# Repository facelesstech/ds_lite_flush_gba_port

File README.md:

# ds_lite_flush_gba_port
ds_lite_flush_gba_port

Blog post - https://facelesstech.wordpress.com/2022/10/15/gameboy-macro-with-a-flush-gba-port/

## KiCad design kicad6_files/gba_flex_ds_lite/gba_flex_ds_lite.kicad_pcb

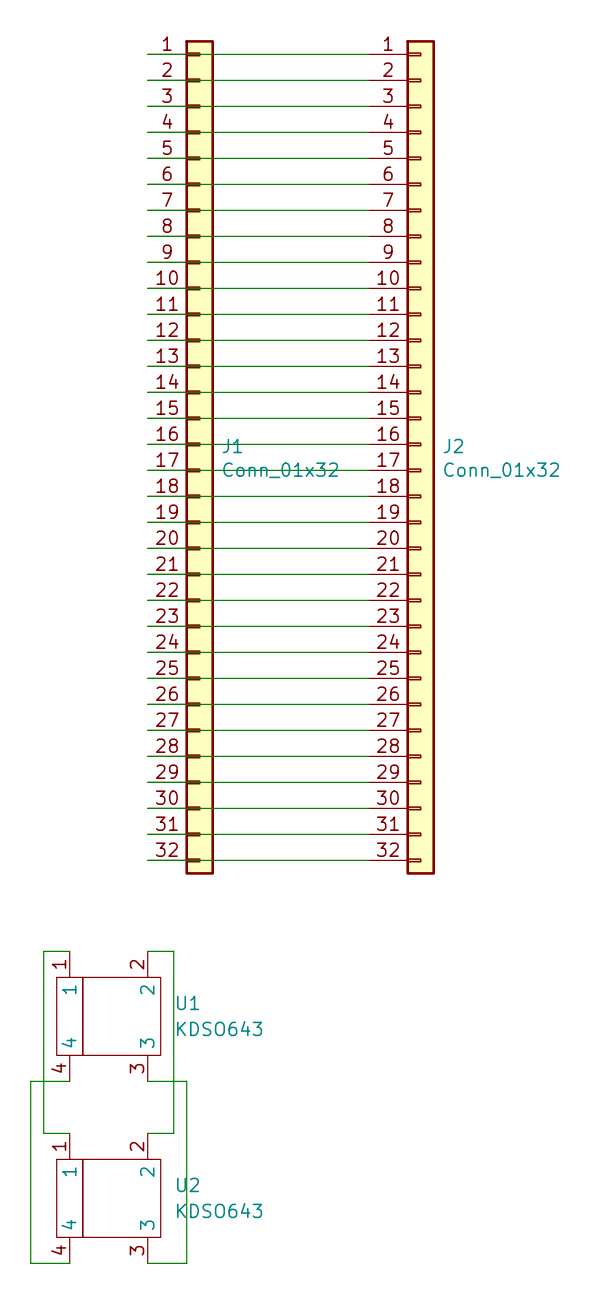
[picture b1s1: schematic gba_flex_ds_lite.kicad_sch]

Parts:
J1: Conn_01x32; GBBus_small
J2: Conn_01x32; GBBus_small_through_hole
U1: KDSO643; ds_lite_crystal_KDSO643_TH
U2: KDSO643; ds_lite_crystal_KDSO643_SMD

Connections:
unnamed: J1.1, J2.1
unnamed: J1.2, J2.2
unnamed: J1.3, J2.3
unnamed: J1.4, J2.4
unnamed: J1.5, J2.5
unnamed: J1.6, J2.6
unnamed: J1.7, J2.7
unnamed: J1.8, J2.8
unnamed: J1.9, J2.9
unnamed: J1.10, J2.10
unnamed: J1.11, J2.11
unnamed: J1.12, J2.12
unnamed: J1.13, J2.13
unnamed: J1.14, J2.14
unnamed: J1.15, J2.15
unnamed: J1.16, J2.16
unnamed: J1.17, J2.17
unnamed: J1.18, J2.18
unnamed: J1.19, J2.19
unnamed: J1.20, J2.20
unnamed: J1.21, J2.21
unnamed: J1.22, J2.22
unnamed: J1.23, J2.23
unnamed: J1.24, J2.24
unnamed: J1.25, J2.25
unnamed: J1.26, J2.26
unnamed: J1.27, J2.27
unnamed: J1.28, J2.28
unnamed: J1.29, J2.29
unnamed: J1.30, J2.30
unnamed: J1.31, J2.31
unnamed: J1.32, J2.32
unnamed: U1.1, U2.1
unnamed: U1.2, U2.2
unnamed: U1.3, U2.3
unnamed: U1.4, U2.4

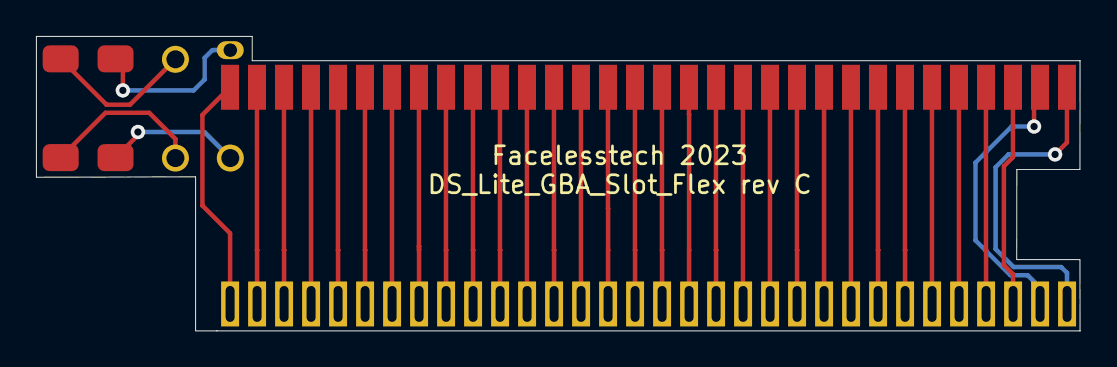
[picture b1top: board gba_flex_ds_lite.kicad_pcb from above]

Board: 2 copper layers, 58.0 x 16.4 mm, 4 parts (0 on the bottom side), 36 nets.

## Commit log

2022-10-13 added license
2022-10-13 Flex PCB files
2022-10-16 added blog post link
2022-10-16 added a photo
2022-10-16 added photo to readme
2022-10-16 added photo to readme1
2022-10-16 added another photo
2024-03-01 updated board and gerbers files to latest version
2024-03-02 updated gerber files folder
2024-03-02 updated gerber files zip file
